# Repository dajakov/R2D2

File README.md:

# R2D2 Robotic Control System

<div style="display: flex; justify-content: space-between;">

</div>

This repository contains all source files for a robotic control system designed to control a life-sized R2D2 robot. The 3D models were created by  [Michael Baddeley](https://www.patreon.com/mrbaddeley).

I initiated this project due to the need for a smart and reliable way to control R2D2 via an Android app. I began developing a simple proof-of-concept app in Android Studio, featuring:

- A joystick for velocity control
- Two buttons to rotate the dome
- A text field to display debugging messages

The communication between the hardware and the app occurs via a WebSocket connection to an ESP01.

# Hardware

I designed multiple subsystems, each with its own PCB. The brain of every subsystem is a STM32 microcontroller, responsible for fulfilling unique tasks. These PCBs communicate with each other via CAN-bus.

The main PCB serves as the translator for incoming data from the Android app, converting it into low-level commands for the subsystems which control the actual hardware. 

# Firmware

The STM32 microcontrollers were programmed using STM32CubeIDE. This repository contains the entire CubeIDE project directory for each subsystem.
Each PCB features a 2.54mm male pin header, allowing for easy flashing and debugging via SWD (Serial Wire Debug).

# Development

Hardware:
- [x] Test main PCB
- [x] Test drive PCB
- [ ] Test dome-motor PCB
- [x] Test drive-intelligence PCB
- [ ] Test battery-control PCB

Firmware:
- [x] Velocity control 
- [x] Shut down motors on connection loss to Android App
- [x] Increase CAN frequency

Android App:
- [x] Joystick
- [x] Buttons for dome rotation
- [ ] Add status display (battery state, error indicator)

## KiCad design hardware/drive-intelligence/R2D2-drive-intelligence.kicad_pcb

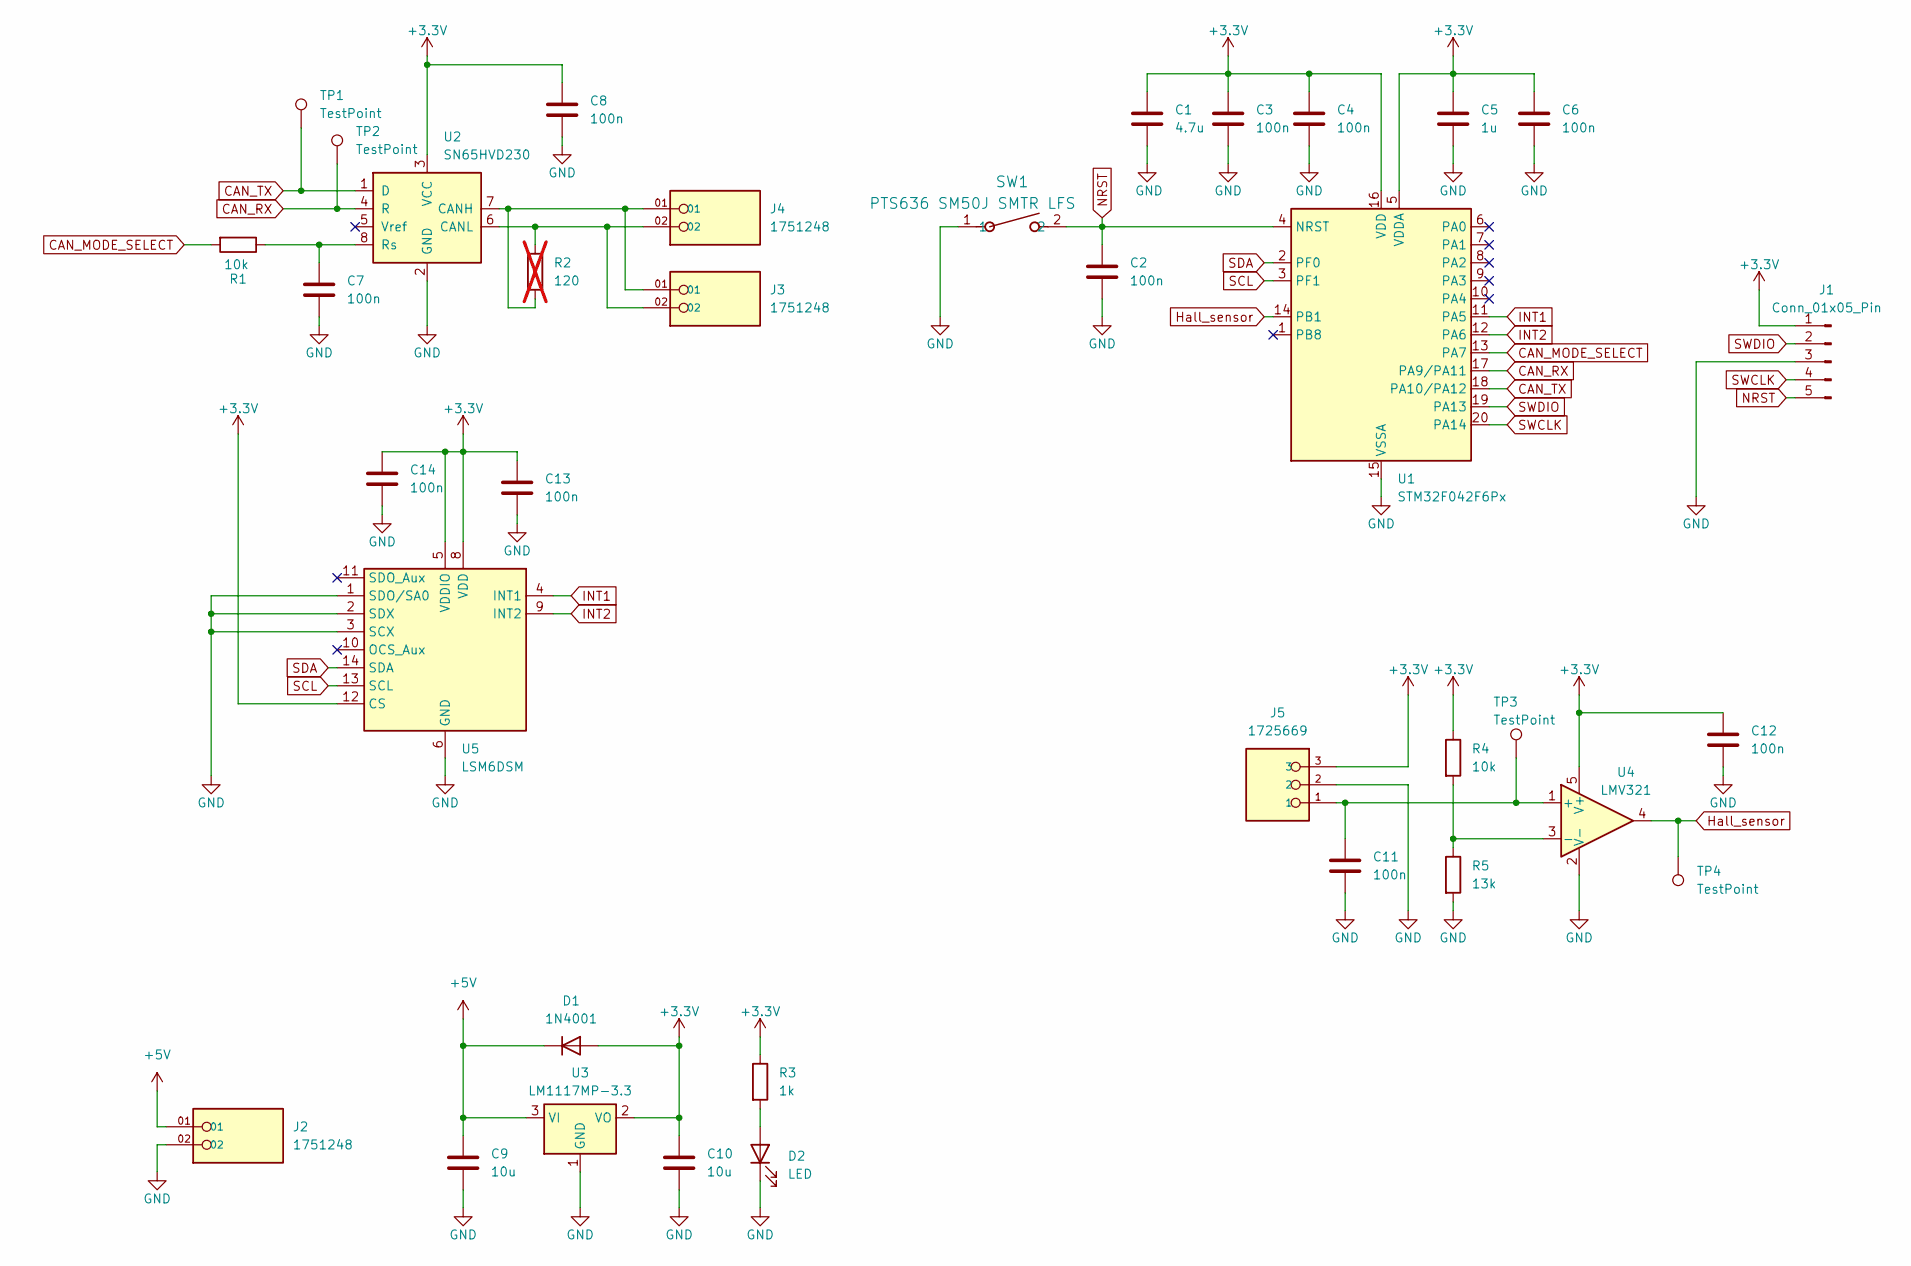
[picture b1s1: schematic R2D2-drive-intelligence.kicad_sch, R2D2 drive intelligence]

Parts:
C1: 4.7u; C_0603_1608Metric_Pad1.08x0.95mm_HandSolder
C2, C3, C4, C6, C7, C8, C11, C12, C13, C14: 100n; C_0603_1608Metric_Pad1.08x0.95mm_HandSolder
C5: 1u; C_0603_1608Metric_Pad1.08x0.95mm_HandSolder
C9, C10: 10u; C_0603_1608Metric_Pad1.08x0.95mm_HandSolder
D1: 1N4001; D_SMA_Handsoldering
D2: LED; LED_0603_1608Metric_Pad1.05x0.95mm_HandSolder
J1: Conn_01x05_Pin; PinHeader_1x05_P2.54mm_Horizontal
J2, J3, J4: 1751248; PHOENIX_1751248; PARTREV 03.03.2021
J5: 1725669; PHOENIX_1725669; PARTREV 03.03.2021
R1, R4: 10k; R_0603_1608Metric_Pad0.98x0.95mm_HandSolder
R2: 120; R_0603_1608Metric_Pad0.98x0.95mm_HandSolder; not fitted
R3: 1k; R_0603_1608Metric_Pad0.98x0.95mm_HandSolder
R5: 13k; R_0603_1608Metric_Pad0.98x0.95mm_HandSolder
SW1: PTS636 SM50J SMTR LFS; SW_PTS636_CNK
TP1, TP2, TP3, TP4: TestPoint; TestPoint_Pad_D1.0mm
U1: STM32F042F6Px; TSSOP-20_4.4x6.5mm_P0.65mm
U2: SN65HVD230; SOIC-8_3.9x4.9mm_P1.27mm
U3: LM1117MP-3.3; SOT-223-3_TabPin2
U4: LMV321; SOT-23-5
U5: LSM6DSM; LGA-14_3x2.5mm_P0.5mm_LayoutBorder3x4y

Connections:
+3.3V: C1.1, C3.1, C4.1, C5.1, C6.1, C8.1, C10.1, C12.1, C13.1, C14.1, D1.2 (A), J1.1, J5.3, R3.1, R4.1, U1.5 (VDDA), U1.16 (VDD), U2.3 (VCC), U3.2 (VO), U4.5 (V+), U5.5 (VDDIO), U5.8 (VDD), U5.12 (CS)
+5V: C9.1, D1.1 (K), J2.01, U3.3 (VI)
CAN_MODE_SELECT: R1.2, U1.13 (PA7)
CAN_RX: TP2.1, U1.17 (PA9/PA11), U2.4 (R)
CAN_TX: TP1.1, U1.18 (PA10/PA12), U2.1 (D)
GND: C1.2, C2.2, C3.2, C4.2, C5.2, C6.2, C7.2, C8.2, C9.2, C10.2, C11.2, C12.2, C13.2, C14.2, D2.1 (K), J1.3, J2.02, J5.2, R5.2, SW1.1, U1.15 (VSSA), U2.2 (GND), U3.1 (GND), U4.2 (V-), U5.1 (SDO/SA0), U5.2 (SDX), U5.3 (SCX), U5.6 (GND), U5.7 (GND); also elsewhere on the board
Hall_sensor: TP4.1, U1.14 (PB1), U4.4
INT1: U1.11 (PA5), U5.4 (INT1)
INT2: U1.12 (PA6), U5.9 (INT2)
NRST: C2.1, J1.5, SW1.2, U1.4 (NRST)
unnamed: D2.2 (A), R3.2
unnamed 11: U1.1 (PB8); also elsewhere on the board
unnamed: J3.01, J4.01, R2.2, U2.7 (CANH)
unnamed: J3.02, J4.02, R2.1, U2.6 (CANL)
unnamed: C7.1, R1.1, U2.8 (Rs)
unnamed: C11.1, J5.1, TP3.1, U4.1 (+)
unnamed: R4.2, R5.1, U4.3 (-)
SCL: U1.3 (PF1), U5.13 (SCL)
SDA: U1.2 (PF0), U5.14 (SDA)
SWCLK: J1.4, U1.20 (PA14)
SWDIO: J1.2, U1.19 (PA13)

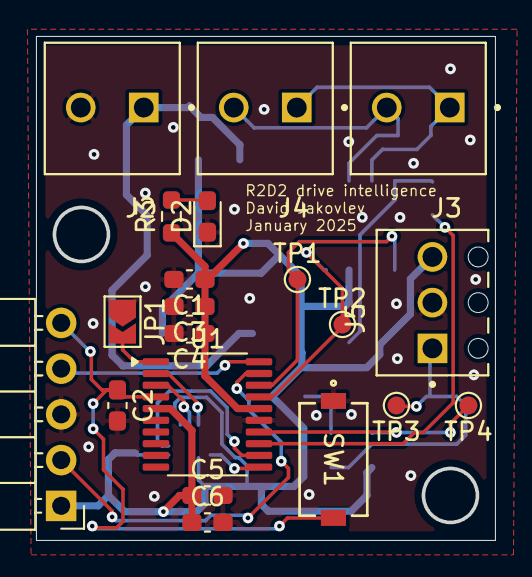
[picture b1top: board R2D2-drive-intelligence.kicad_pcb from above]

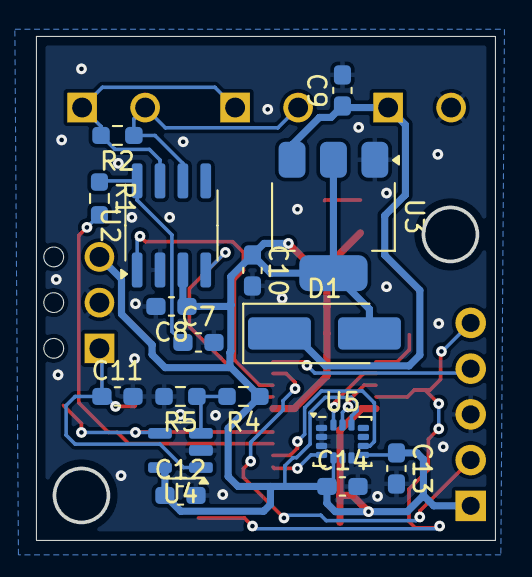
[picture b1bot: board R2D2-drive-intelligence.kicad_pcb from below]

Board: 2 copper layers, 25.4 x 27.9 mm, 37 parts (17 on the bottom side), 21 nets.

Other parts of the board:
JP1: CAN address; SolderJumper-2_P1.3mm_Open_TrianglePad1.0x1.5mm

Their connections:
GND: JP1.1 (A); also elsewhere on the board
unnamed 11: JP1.2 (B); also elsewhere on the board

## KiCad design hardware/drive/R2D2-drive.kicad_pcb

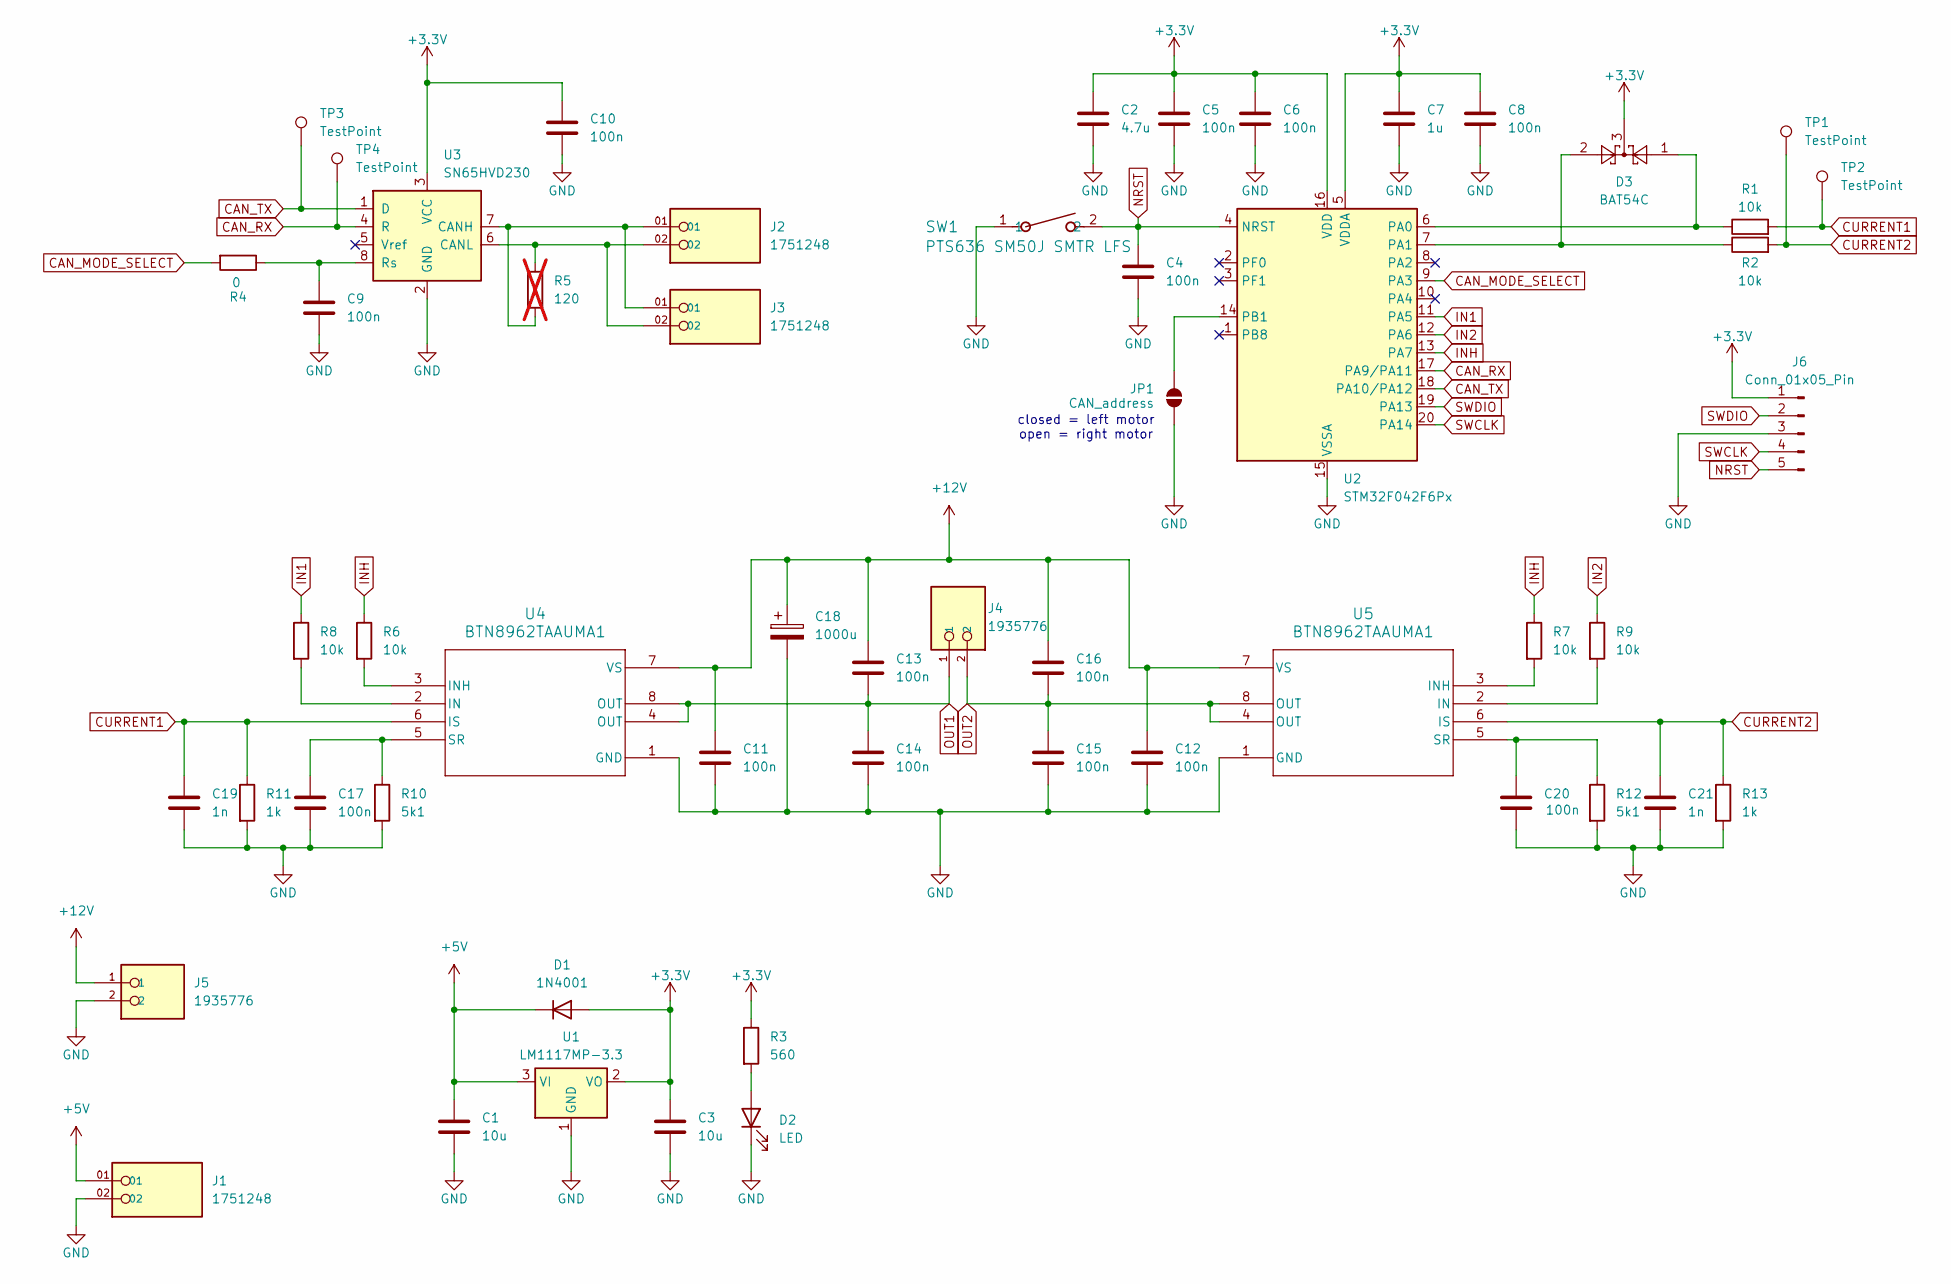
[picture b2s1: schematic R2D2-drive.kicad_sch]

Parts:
C1, C3: 10u; C_0603_1608Metric_Pad1.08x0.95mm_HandSolder
C2: 4.7u; C_0603_1608Metric_Pad1.08x0.95mm_HandSolder
C4, C5, C6, C8, C9, C10, C11, C12, C13, C14, C15, C16, C17, C20: 100n; C_0603_1608Metric_Pad1.08x0.95mm_HandSolder
C7: 1u; C_0603_1608Metric_Pad1.08x0.95mm_HandSolder
C18: 1000u; CP_Elec_10x10.5
C19, C21: 1n; C_0603_1608Metric_Pad1.08x0.95mm_HandSolder
D1: 1N4001; D_SMA_Handsoldering
D2: LED; LED_0603_1608Metric_Pad1.05x0.95mm_HandSolder
D3: BAT54C; SOT-23
J1, J2, J3: 1751248; PHOENIX_1751248; PARTREV 03.03.2021
J4, J5: 1935776; PHOENIX_1935776; PARTREV 19.10.2016
J6: Conn_01x05_Pin; PinHeader_1x05_P2.54mm_Horizontal
JP1: CAN_address; SolderJumper-2_P1.3mm_Open_TrianglePad1.0x1.5mm
R1, R2, R6, R7, R8, R9: 10k; R_0603_1608Metric_Pad0.98x0.95mm_HandSolder
R3: 560; R_0603_1608Metric_Pad0.98x0.95mm_HandSolder
R4: 0; R_0603_1608Metric_Pad0.98x0.95mm_HandSolder
R5: 120; R_0603_1608Metric_Pad0.98x0.95mm_HandSolder; not fitted
R10, R12: 5k1; R_0603_1608Metric_Pad0.98x0.95mm_HandSolder
R11, R13: 1k; R_0603_1608Metric_Pad0.98x0.95mm_HandSolder
SW1: PTS636 SM50J SMTR LFS; SW_PTS636_CNK
TP1, TP2, TP3, TP4: TestPoint; TestPoint_Pad_D1.0mm
U1: LM1117MP-3.3; SOT-223-3_TabPin2
U2: STM32F042F6Px; TSSOP-20_4.4x6.5mm_P0.65mm
U3: SN65HVD230; SOIC-8_3.9x4.9mm_P1.27mm
U4, U5: BTN8962TAAUMA1; PG-TO263-7-1_INF

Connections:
+3.3V: C2.1, C3.1, C5.1, C6.1, C7.1, C8.1, C10.1, D1.2 (A), D3.3, J6.1, R3.1, U1.2 (VO), U2.5 (VDDA), U2.16 (VDD), U3.3 (VCC)
+5V: C1.1, D1.1 (K), J1.01, U1.3 (VI)
+12V: C11.1, C12.1, C13.1, C16.1, C18.1, J5.1, U4.7 (VS), U5.7 (VS)
CAN_MODE_SELECT: R4.2, U2.9 (PA3)
CAN_RX: TP4.1, U2.17 (PA9/PA11), U3.4 (R)
CAN_TX: TP3.1, U2.18 (PA10/PA12), U3.1 (D)
CURRENT1: C19.1, R1.2, R11.1, TP2.1, U4.6 (IS)
CURRENT2: C21.1, R2.2, R13.1, TP1.1, U5.6 (IS)
GND: C1.2, C2.2, C3.2, C4.2, C5.2, C6.2, C7.2, C8.2, C9.2, C10.2, C11.2, C12.2, C14.2, C15.2, C17.2, C18.2, C19.2, C20.2, C21.2, D2.1 (K), J1.02, J5.2, J6.3, JP1.1 (A), R10.2, R11.2, R12.2, R13.2, SW1.1, U1.1 (GND), U2.15 (VSSA), U3.2 (GND), U4.1 (GND), U5.1 (GND)
IN1: R8.1, U2.11 (PA5)
IN2: R9.1, U2.12 (PA6)
INH: R6.1, R7.1, U2.13 (PA7)
NRST: C4.1, J6.5, SW1.2, U2.4 (NRST)
unnamed: D2.2 (A), R3.2
unnamed: JP1.2 (B), U2.14 (PB1)
unnamed: D3.1, R1.1, U2.6 (PA0)
unnamed: D3.2, R2.1, U2.7 (PA1)
unnamed: J2.01, J3.01, R5.2, U3.7 (CANH)
unnamed: J2.02, J3.02, R5.1, U3.6 (CANL)
unnamed: C9.1, R4.1, U3.8 (Rs)
unnamed: R8.2, U4.2 (IN)
unnamed: R6.2, U4.3 (INH)
unnamed: C17.1, R10.1, U4.5 (SR)
unnamed: R9.2, U5.2 (IN)
unnamed: R7.2, U5.3 (INH)
unnamed: C20.1, R12.1, U5.5 (SR)
OUT1: C13.2, C14.1, J4.1, U4.4 (OUT), U4.8 (OUT)
OUT2: C15.1, C16.2, J4.2, U5.4 (OUT), U5.8 (OUT)
SWCLK: J6.4, U2.20 (PA14)
SWDIO: J6.2, U2.19 (PA13)

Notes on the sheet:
closed = left motor open = right motor

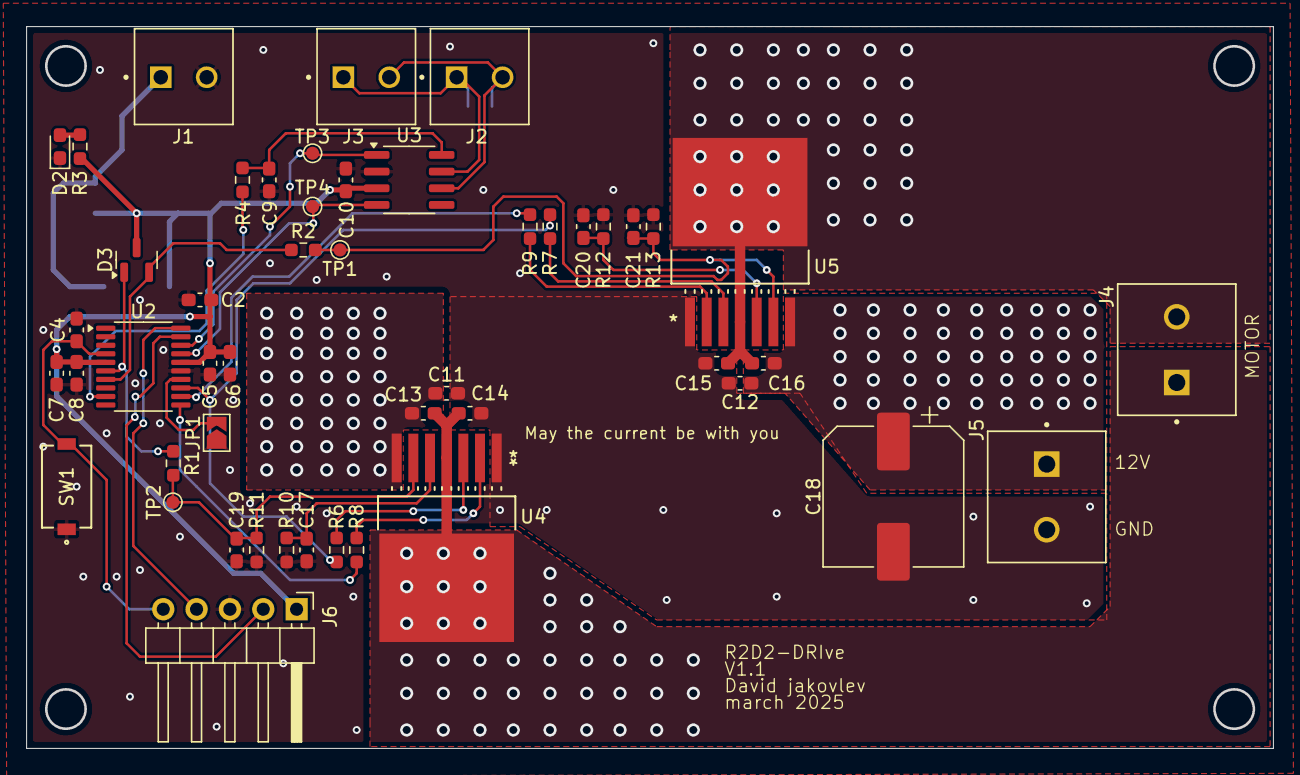
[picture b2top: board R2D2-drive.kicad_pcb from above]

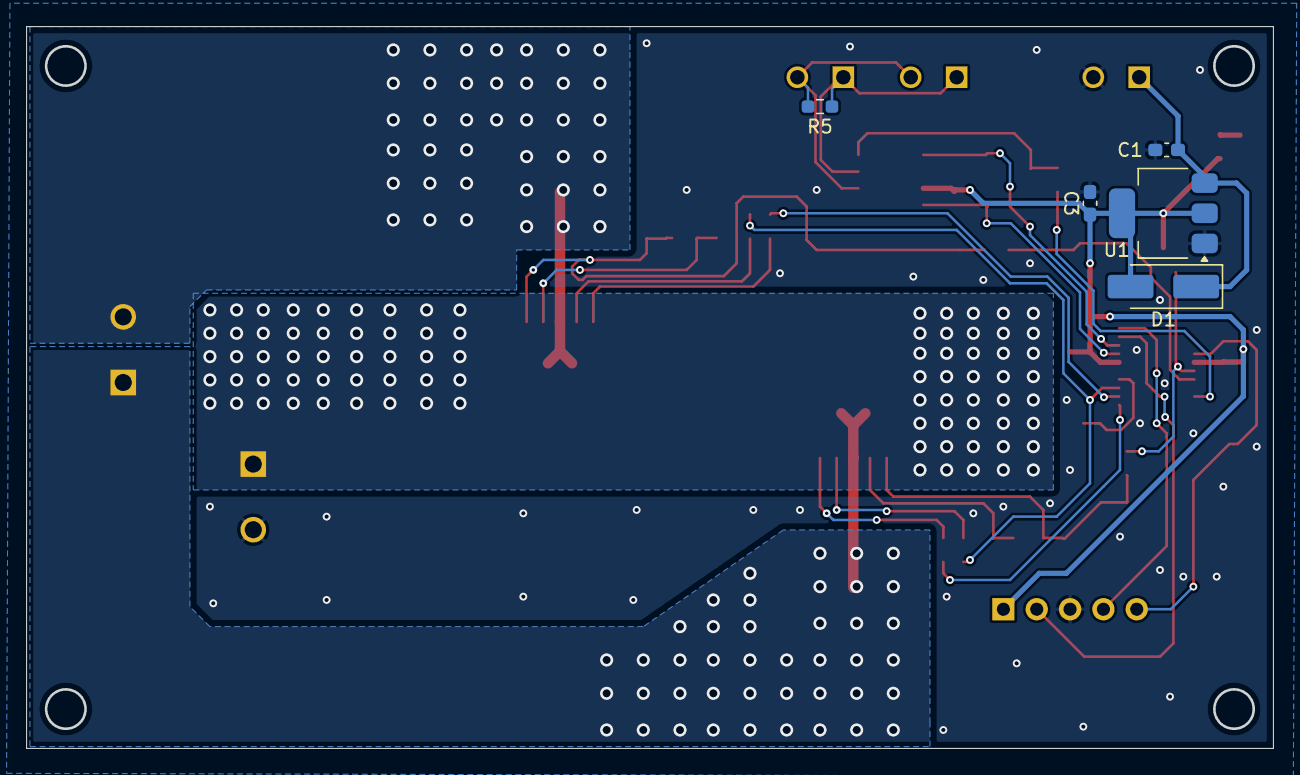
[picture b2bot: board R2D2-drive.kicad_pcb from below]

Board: 2 copper layers, 94.9 x 54.9 mm, 54 parts (5 on the bottom side), 30 nets.

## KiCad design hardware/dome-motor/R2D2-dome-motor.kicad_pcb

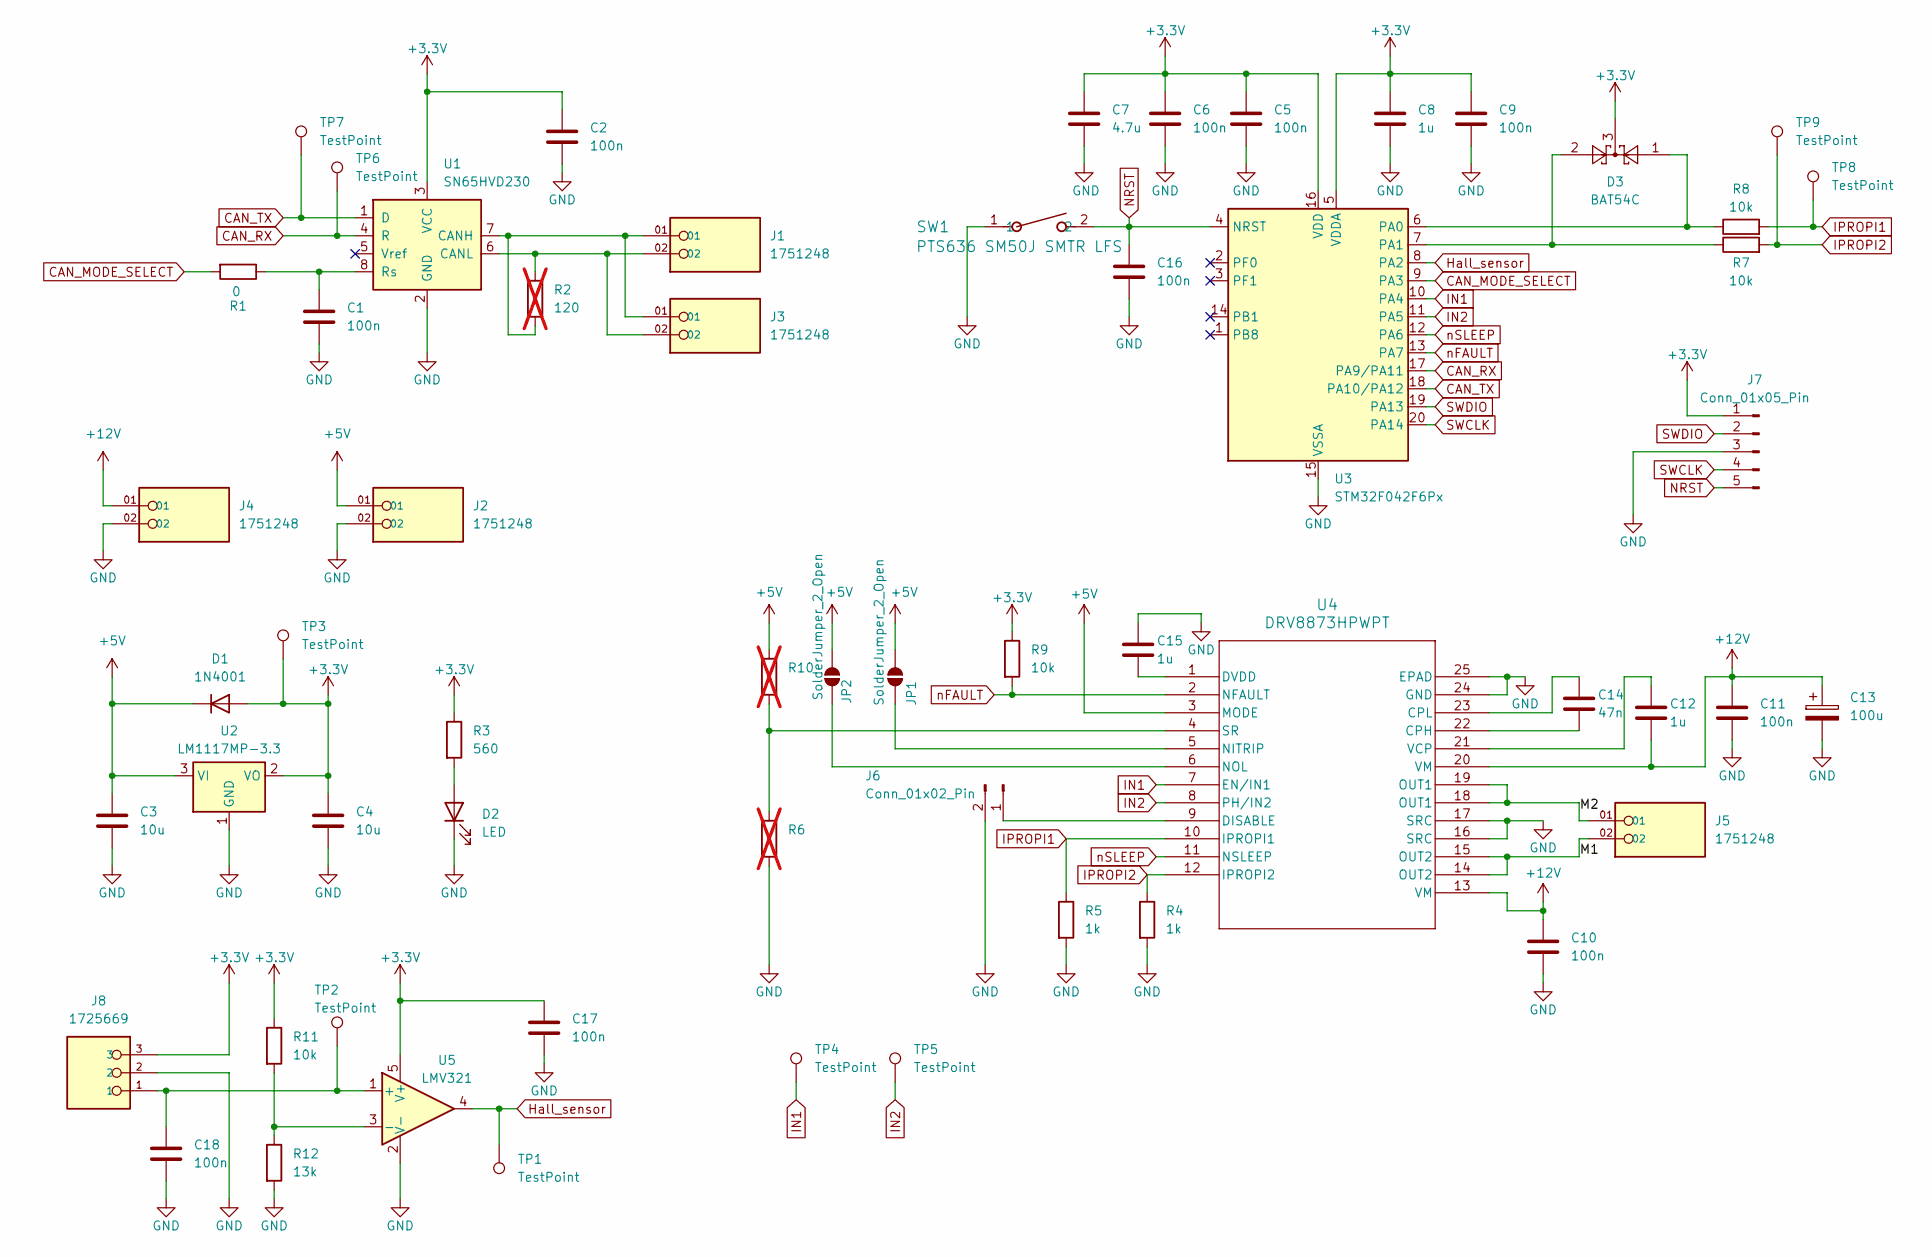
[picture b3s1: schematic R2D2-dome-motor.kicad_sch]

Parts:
C1, C2, C5, C6, C9, C16, C17, C18: 100n; C_0603_1608Metric_Pad1.08x0.95mm_HandSolder
C3, C4: 10u; C_0603_1608Metric_Pad1.08x0.95mm_HandSolder
C7: 4.7u; C_0603_1608Metric_Pad1.08x0.95mm_HandSolder
C8, C15: 1u; C_0603_1608Metric_Pad1.08x0.95mm_HandSolder
C10, C11: 100n; C_0603_1608Metric
C12: 1u; C_0603_1608Metric
C13: 100u; CP_Elec_8x10.5
C14: 47n; C_0603_1608Metric
D1: 1N4001; D_SMA_Handsoldering
D2: LED; LED_0603_1608Metric_Pad1.05x0.95mm_HandSolder
D3: BAT54C; SOT-23
J1, J2, J3, J4, J5: 1751248; PHOENIX_1751248; PARTREV 03.03.2021
J6: Conn_01x02_Pin; PinSocket_1x02_P2.54mm_Vertical
J7: Conn_01x05_Pin; PinHeader_1x05_P2.54mm_Vertical
J8: 1725669; PHOENIX_1725669; PARTREV 03.03.2021
JP1, JP2: SolderJumper_2_Open; SolderJumper-2_P1.3mm_Open_TrianglePad1.0x1.5mm
R1: 0; R_0603_1608Metric_Pad0.98x0.95mm_HandSolder
R2: 120; R_0603_1608Metric_Pad0.98x0.95mm_HandSolder; not fitted
R3: 560; R_0603_1608Metric_Pad0.98x0.95mm_HandSolder
R4, R5: 1k; R_0603_1608Metric_Pad0.98x0.95mm_HandSolder
R6, R10: R_0603_1608Metric_Pad0.98x0.95mm_HandSolder; not fitted
R7, R8, R9, R11: 10k; R_0603_1608Metric_Pad0.98x0.95mm_HandSolder
R12: 13k; R_0603_1608Metric_Pad0.98x0.95mm_HandSolder
SW1: PTS636 SM50J SMTR LFS; SW_PTS636_CNK
TP1, TP2, TP3, TP4, TP5, TP6, TP7, TP8, TP9: TestPoint; TestPoint_Pad_D1.0mm
U1: SN65HVD230; SOIC-8_3.9x4.9mm_P1.27mm
U2: LM1117MP-3.3; SOT-223-3_TabPin2
U3: STM32F042F6Px; TSSOP-20_4.4x6.5mm_P0.65mm
U4: DRV8873HPWPT; PWP24_TEX-M
U5: LMV321; SOT-23-5

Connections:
+3.3V: C2.1, C4.1, C5.1, C6.1, C7.1, C8.1, C9.1, C17.1, D1.2 (A), D3.3, J7.1, J8.3, R3.1, R9.1, R11.1, TP3.1, U1.3 (VCC), U2.2 (VO), U3.5 (VDDA), U3.16 (VDD), U5.5 (V+)
+5V: C3.1, D1.1 (K), J2.01, JP1.2 (B), JP2.2 (B), R10.1, U2.3 (VI), U4.3 (MODE)
+12V: C10.1, C11.1, C12.2, C13.1, J4.01, U4.13 (VM), U4.20 (VM)
/M1: J5.02, U4.14 (OUT2), U4.15 (OUT2)
/M2: J5.01, U4.18 (OUT1), U4.19 (OUT1)
CAN_MODE_SELECT: R1.2, U3.9 (PA3)
CAN_RX: TP6.1, U1.4 (R), U3.17 (PA9/PA11)
CAN_TX: TP7.1, U1.1 (D), U3.18 (PA10/PA12)
GND: C1.2, C2.2, C3.2, C4.2, C5.2, C6.2, C7.2, C8.2, C9.2, C10.2, C11.2, C13.2, C15.1, C16.2, C17.2, C18.2, D2.1 (K), J2.02, J4.02, J6.2, J7.3, J8.2, R4.2, R5.2, R6.2, R12.2, SW1.1, U1.2 (GND), U2.1 (GND), U3.15 (VSSA), U4.16 (SRC), U4.17 (SRC), U4.24 (GND), U4.25 (EPAD), U5.2 (V-)
Hall_sensor: TP1.1, U3.8 (PA2), U5.4
IN1: TP4.1, U3.10 (PA4), U4.7 (EN/IN1)
IN2: TP5.1, U3.11 (PA5), U4.8 (PH/IN2)
IPROPI1: R5.1, R8.2, TP8.1, U4.10 (IPROPI1)
IPROPI2: R4.1, R7.2, TP9.1, U4.12 (IPROPI2)
NRST: C16.1, J7.5, SW1.2, U3.4 (NRST)
unnamed: D2.2 (A), R3.2
unnamed: J6.1, U4.9 (DISABLE)
unnamed: JP1.1 (A), U4.5 (NITRIP)
unnamed: JP2.1 (A), U4.6 (NOL)
unnamed: J1.01, J3.01, R2.2, U1.7 (CANH)
unnamed: J1.02, J3.02, R2.1, U1.6 (CANL)
unnamed: C1.1, R1.1, U1.8 (Rs)
unnamed: D3.1, R8.1, U3.6 (PA0)
unnamed: D3.2, R7.1, U3.7 (PA1)
unnamed: C14.2, U4.22 (CPH)
unnamed: C14.1, U4.23 (CPL)
unnamed: C15.2, U4.1 (DVDD)
unnamed: R6.1, R10.2, U4.4 (SR)
unnamed: C12.1, U4.21 (VCP)
unnamed: C18.1, J8.1, TP2.1, U5.1 (+)
unnamed: R11.2, R12.1, U5.3 (-)
SWCLK: J7.4, U3.20 (PA14)
SWDIO: J7.2, U3.19 (PA13)
nFAULT: R9.2, U3.13 (PA7), U4.2 (NFAULT)
nSLEEP: U3.12 (PA6), U4.11 (NSLEEP)

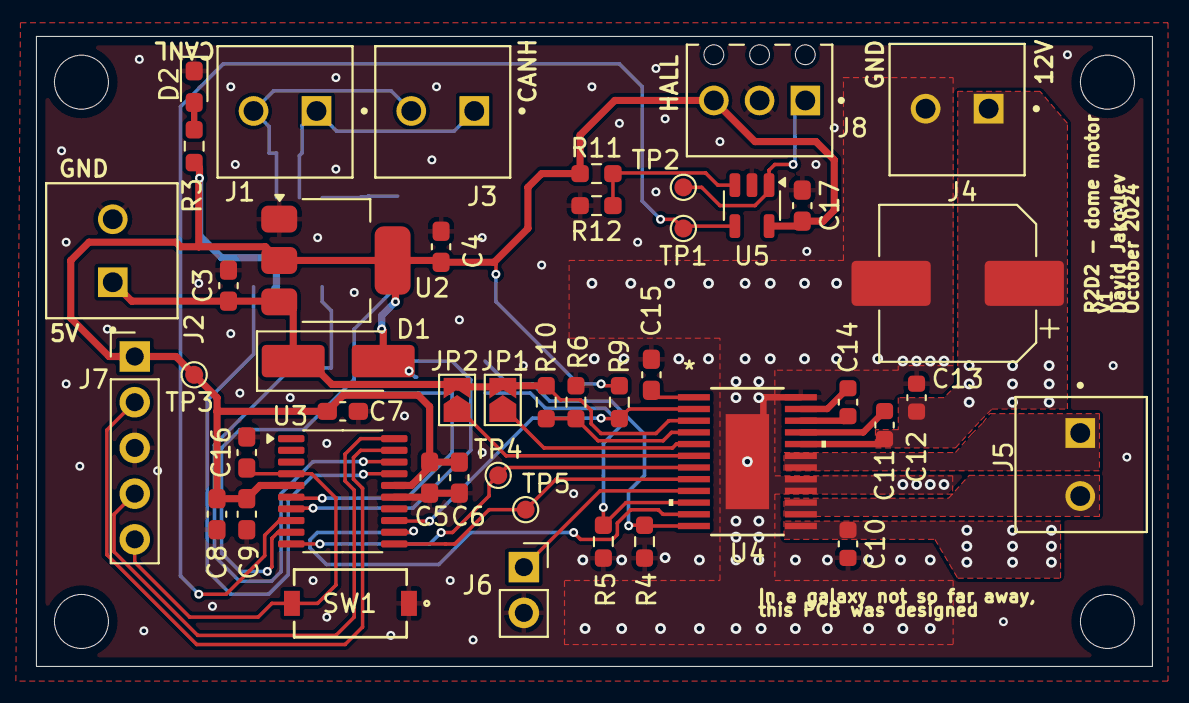
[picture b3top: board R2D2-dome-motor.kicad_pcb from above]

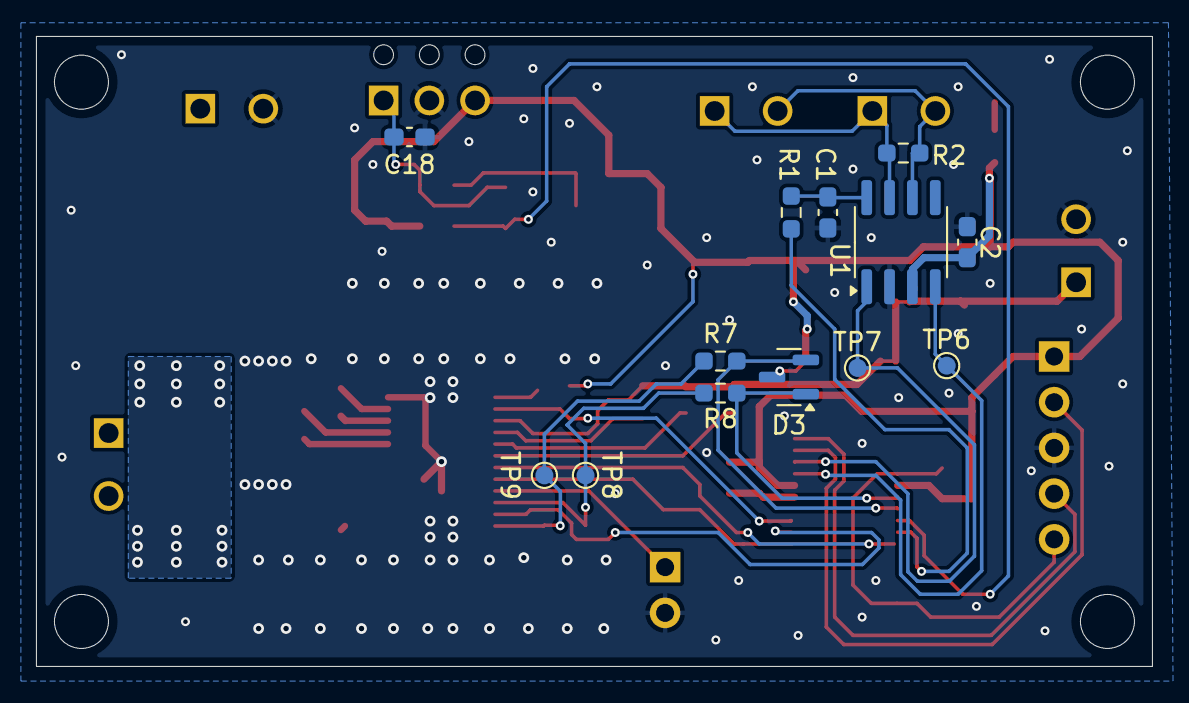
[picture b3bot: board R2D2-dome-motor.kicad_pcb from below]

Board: 2 copper layers, 62.0 x 35.0 mm, 58 parts (13 on the bottom side), 35 nets.

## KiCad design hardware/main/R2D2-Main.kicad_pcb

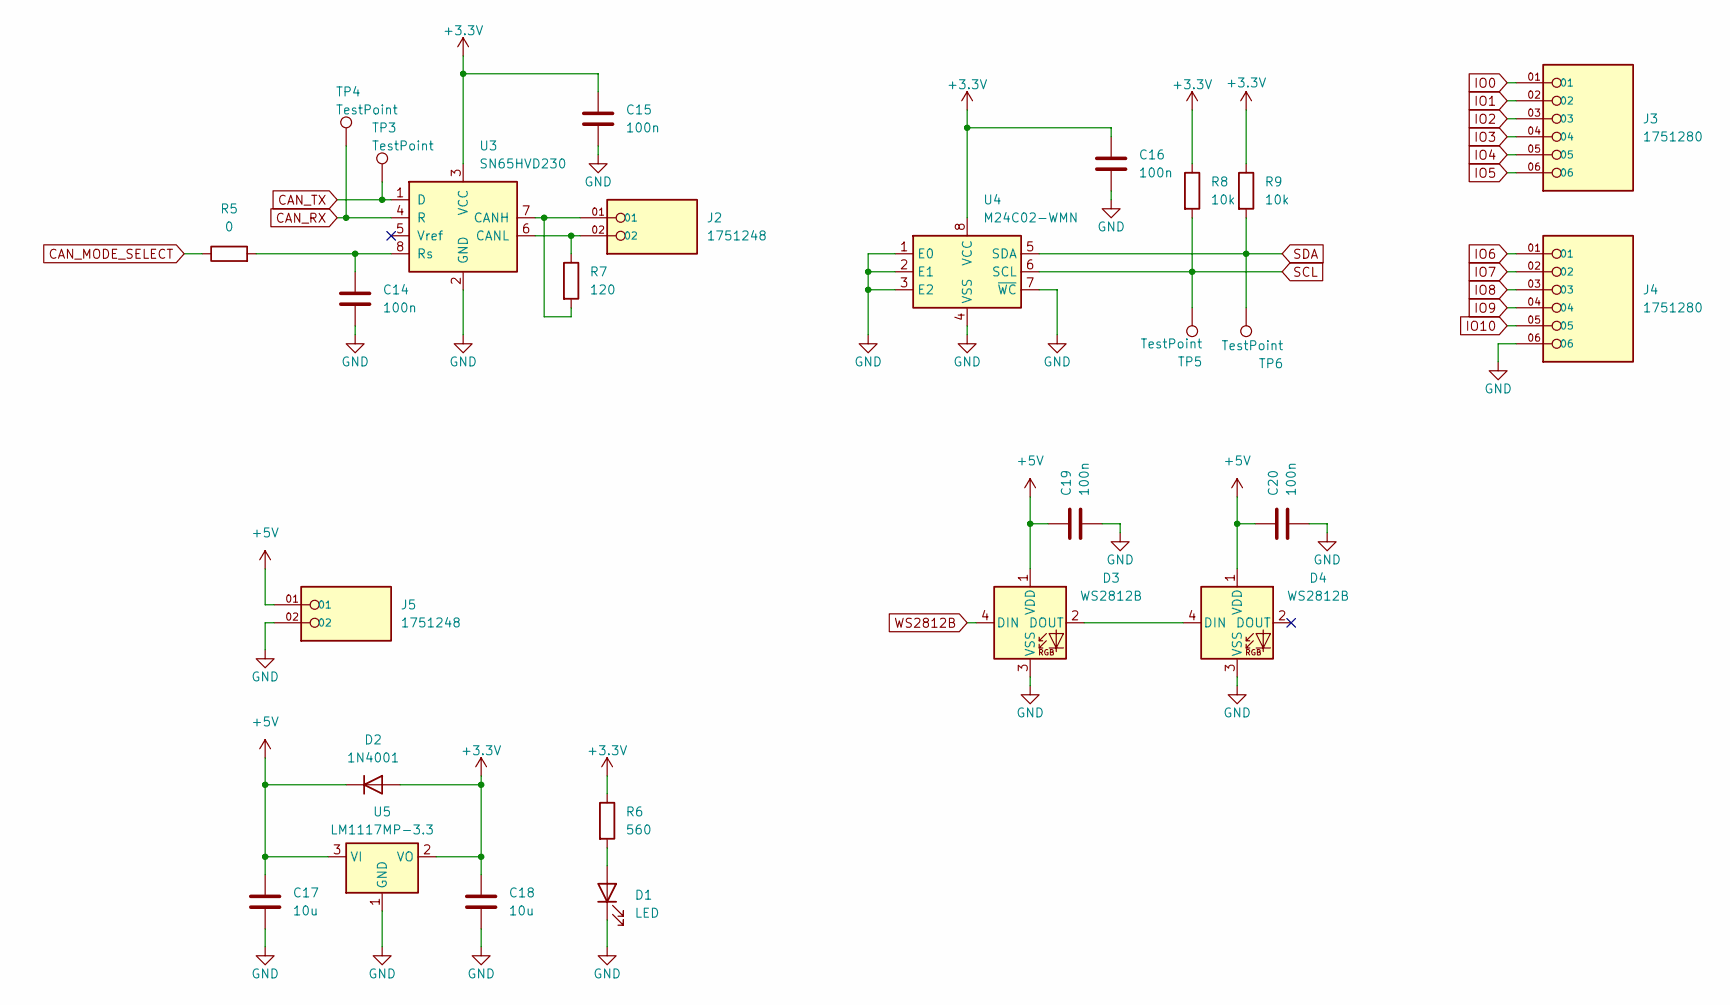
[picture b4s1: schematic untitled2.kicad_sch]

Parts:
C14, C15, C16, C19, C20: 100n; C_0603_1608Metric_Pad1.08x0.95mm_HandSolder
C17, C18: 10u; C_0603_1608Metric_Pad1.08x0.95mm_HandSolder
D1: LED; LED_0603_1608Metric_Pad1.05x0.95mm_HandSolder
D2: 1N4001; D_SMA_Handsoldering
D3, D4: WS2812B; LED_WS2812B_PLCC4_5.0x5.0mm_P3.2mm
J2, J5: 1751248; PHOENIX_1751248; PARTREV 03.03.2021
J3, J4: 1751280; PHOENIX_1751280; PARTREV 03.03.2021
R5: 0; R_0603_1608Metric_Pad0.98x0.95mm_HandSolder
R6: 560; R_0603_1608Metric_Pad0.98x0.95mm_HandSolder
R7: 120; R_0603_1608Metric_Pad0.98x0.95mm_HandSolder
R8, R9: 10k; R_0603_1608Metric_Pad0.98x0.95mm_HandSolder
TP3, TP4, TP5, TP6: TestPoint; TestPoint_Pad_D1.0mm
U3: SN65HVD230; SOIC-8_3.9x4.9mm_P1.27mm
U4: M24C02-WMN; SOIC-8_3.9x4.9mm_P1.27mm
U5: LM1117MP-3.3; SOT-223-3_TabPin2

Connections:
+3.3V: C15.1, C16.1, C18.1, D2.2 (A), R6.1, R8.1, R9.1, U3.3 (VCC), U4.8 (VCC), U5.2 (VO); also elsewhere on the board
+5V: C17.1, C19.1, C20.1, D2.1 (K), D3.1 (VDD), D4.1 (VDD), J5.01, U5.3 (VI)
CAN_MODE_SELECT: R5.1; also elsewhere on the board
CAN_RX: TP4.1, U3.4 (R); also elsewhere on the board
CAN_TX: TP3.1, U3.1 (D); also elsewhere on the board
GND: C14.2, C15.2, C16.2, C17.2, C18.2, C19.2, C20.2, D1.1 (K), D3.3 (VSS), D4.3 (VSS), J4.06, J5.02, U3.2 (GND), U4.1 (E0), U4.2 (E1), U4.3 (E2), U4.4 (VSS), U4.7 (~WC), U5.1 (GND); also elsewhere on the board
IO0: J3.01; also elsewhere on the board
IO1: J3.02; also elsewhere on the board
IO2: J3.03; also elsewhere on the board
IO3: J3.04; also elsewhere on the board
IO4: J3.05; also elsewhere on the board
IO5: J3.06; also elsewhere on the board
IO6: J4.01; also elsewhere on the board
IO7: J4.02; also elsewhere on the board
IO8: J4.03; also elsewhere on the board
IO9: J4.04; also elsewhere on the board
IO10: J4.05; also elsewhere on the board
unnamed: D1.2 (A), R6.2
unnamed: D3.2 (DOUT), D4.4 (DIN)
unnamed: J2.01, R7.2, U3.7 (CANH)
unnamed: J2.02, R7.1, U3.6 (CANL)
unnamed: C14.1, R5.2, U3.8 (Rs)
SCL: R8.2, TP5.1, U4.6 (SCL); also elsewhere on the board
SDA: R9.2, TP6.1, U4.5 (SDA); also elsewhere on the board
WS2812B: D3.4 (DIN); also elsewhere on the board
